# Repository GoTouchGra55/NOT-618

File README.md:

# NOT-618

_A custom CoreXY printer built on hopes and dreams._

**New Object Transmitter-618 / NOT-618** is a medium sized print volume _(220 × 220 × 220 mm)_ custom CoreXY 3d printer developed as a long term engineering project.

The project focuses on reliability, serviceability, and my open-source loyalty while serving as a platform for learning embedded systems, mechanical & PCB design, and firmware engineering.

## Features

- Automatic bed-leveling using BLTouch
- Independent dual Z motors
- Custom STM32F407-based controller (Vulcan-MK1)
- Marlin firmware support
- Fully open source design
- 24V power input

## Mechanical Design

### CAD: [OnShape URL](https://cad.onshape.com/documents/e82edfc86bb0a1665cdc75ee/w/ca3abfddd82f0954c06884bb/e/6fbd4bded61cf9b65a4d5030)

## PCB Design _(Vulcan-MK1)_

For GERBER file see [Vulcan-MK1](PCB/production/Vulcan-MK1.zip)

## Schematics

## Specifications

| Component       | Specification                       |
| --------------- | ----------------------------------- |
| Motion System   | CoreXY                              |
| Build Volume    | 220 × 220 × 220 mm                  |
| MCU             | STM32F407VET6                       |
| Stepper Drivers | TMC2209                             |
| Hotend          | E3D V6                              |
| Heated Bed      | Anycubic Kobra Go 24V               |
| Bed Probe       | BLTouch                             |
| Power Supply    | 24V 15A                             |
| Cooling         | 5015 Part Cooling + 3010 Hotend Fan |

## Assembly guide

1. Refer to the Onshape assembly for component placement and assembly order.
2. Do not carelessly wire the pcb and ensure good solder joints.

## ⚠️ Warning

1. Double-check polarity of capacitors and power input before powering the board. Otherwise you've made a fancy bomb :D
2. Use a 24v 15A SMPS for optimal performance. NEVER go higher than this.

## Flashing the Firmware

### 1. Build the Firmware

Compile Marlin using PlatformIO:

```bash
pio run -e STM32F407VE_black
```

After a successful build, the firmware will be located at:

```
.pio/build/STM32F407VE_black/firmware.bin
```

---

### 2. Copy the Firmware

1. Insert a microSD card (FAT32 formatted).
2. Copy `firmware.bin` to the root directory of the SD card.

The directory should look like:

```
/
├── firmware.bin
```

### 3. Flash the Board

1. Turn **off** the printer.
2. Insert the microSD card into the onboard SD card slot.
3. Power the board.

The STM32 bootloader will automatically detect `firmware.bin` and begin flashing.

Do **not** remove power during this process.

---

### 4. Verify the Flash

After flashing is complete:

- The board should boot into Marlin.
- Connect to the USB serial port.
- Send:

```gcode
M115
```

A successful response should report the installed Marlin version.

## Bill of Materials

| Name                   | Purpose                         | Quantity | Total Cost (USD) | Distributor              |
| ---------------------- | ------------------------------- | -------: | ---------------: | ------------------------ |
| Zip Ties               | Cable management                |        1 |            $1.04 | Daraz Nepal              |
| 22 AWG Wire            | For long connections            |        1 |            $4.08 | Daraz Nepal              |
| 18 AWG Wire            | For power connections           |        1 |            $5.34 | Daraz Nepal              |
| 24V 15A SMPS           | For power delivery              |        1 |           $31.14 | Daraz Nepal              |
| 0603 resistors         | For PCB                         |        1 |            $4.58 | Daraz Nepal              |
| 0805 capacitors        | For PCB                         |        1 |            $5.78 | Daraz Nepal              |
| Pitch Connectors       | For PCB                         |        1 |            $6.12 | Daraz Nepal              |
| JST XH Connectors      | For PCB                         |        1 |            $5.11 | Daraz Nepal              |
| 5015 24V Fan           | For cooling duct                |        1 |            $5.27 | Daraz Nepal              |
| Screws                 | For securing connections        |        1 |           $11.78 | Daraz Nepal              |
| 24V Heated Bed         | For printer                     |        1 |           $19.78 | Daraz Nepal              |
| PEI Sheet              | For printer                     |        1 |           $13.52 | Daraz Nepal              |
| GT2 idler              | For movement                    |        8 |           $25.24 | Daraz Nepal              |
| GT2 belt               | For movement                    |        1 |           $10.99 | Daraz Nepal              |
| E3D Hotend             | For printing                    |        1 |           $11.05 | Daraz Nepal              |
| Timing belt fixer      | For attaching belts             |        1 |             $3.1 | Daraz Nepal              |
| T-Nuts                 | For attaching extrusions        |        1 |            $5.84 | Daraz Nepal              |
| MK8 Extruder           | For filament output             |        1 |           $12.14 | Daraz Nepal              |
| Pancake Stepper        | For MK8 extruder                |        1 |           $12.04 | Daraz Nepal              |
| 3015 Fan               | For hotend cooling              |        1 |            $3.14 | Daraz Nepal              |
| Brass Inserts          | For fasteners                   |        1 |            $8.89 | Daraz Nepal              |
| Allen Keys             | For securing hex nuts           |        1 |            $1.75 | Daraz Nepal              |
| Limit switches         | For min-max feedback            |        2 |            $3.92 | Daraz Nepal              |
| Motor Coupler          | For attaching steppers and rods |        2 |            $2.44 | Daraz Nepal              |
| Threaded Rods          | For Z-axis movement             |        2 |            $7.54 | Daraz Nepal              |
| GT2 pulley             | For steppers                    |        2 |            $1.57 | Daraz Nepal              |
| Stepper Motors         | For movement                    |        4 |           $51.95 | Daraz Nepal              |
| LM10UU Bearings        | For linear movement             |        8 |           $18.49 | Daraz Nepal              |
| LM12UU Bearings        | For linear movement             |        4 |           $11.99 | Daraz Nepal              |
| Linear Shaft (300mm)   | For linear movement (12mm)      |        4 |           $67.98 | Daraz Nepal              |
| Linear Shaft (500mm)   | For linear movement (10mm)      |        2 |           $27.06 | Daraz Nepal              |
| Linear Shaft (330mm)   | For linear movement (10mm)      |        2 |           $19.10 | Daraz Nepal              |
| BLTouch                | For auto-bed leveling           |        1 |           $12.74 | Daraz Nepal              |
| 2040 Extrusion         | For printer stability           |        1 |              $15 | Daraz Nepal              |
| 2020 Extrusion (800mm) | Printer frame                   |        5 |          $117.08 | Daraz Nepal              |
| 2020 Extrusion (600mm) | Printer frame                   |        5 |          $104.98 | Daraz Nepal              |
| TMC2209 drivers        | To drive motors                 |        5 |           $37.26 | Daraz Nepal              |
| 12864 LCD              | To display stuff                |        1 |           $35.39 | Daraz Nepal              |
| 3-Way Connector        | To connect corners of extrusion |        8 |           $17.53 | Daraz Nepal              |
| Vulcan-MK1 PCB         | To control printer              |        1 |          $151.24 | JLCPCB                   |
| **Shipping**           |                                 |          |       **$29.72** | **Daraz Nepal & JLCPCB** |
| **Total**              |                                 |          |      **$944.16** |                          |

## License

### MIT-License - See [LICENSE](/LICENSE)

## Author 🧑‍💻

### [Shaurya Tamang](https://shauryatamang.netlify.app/)

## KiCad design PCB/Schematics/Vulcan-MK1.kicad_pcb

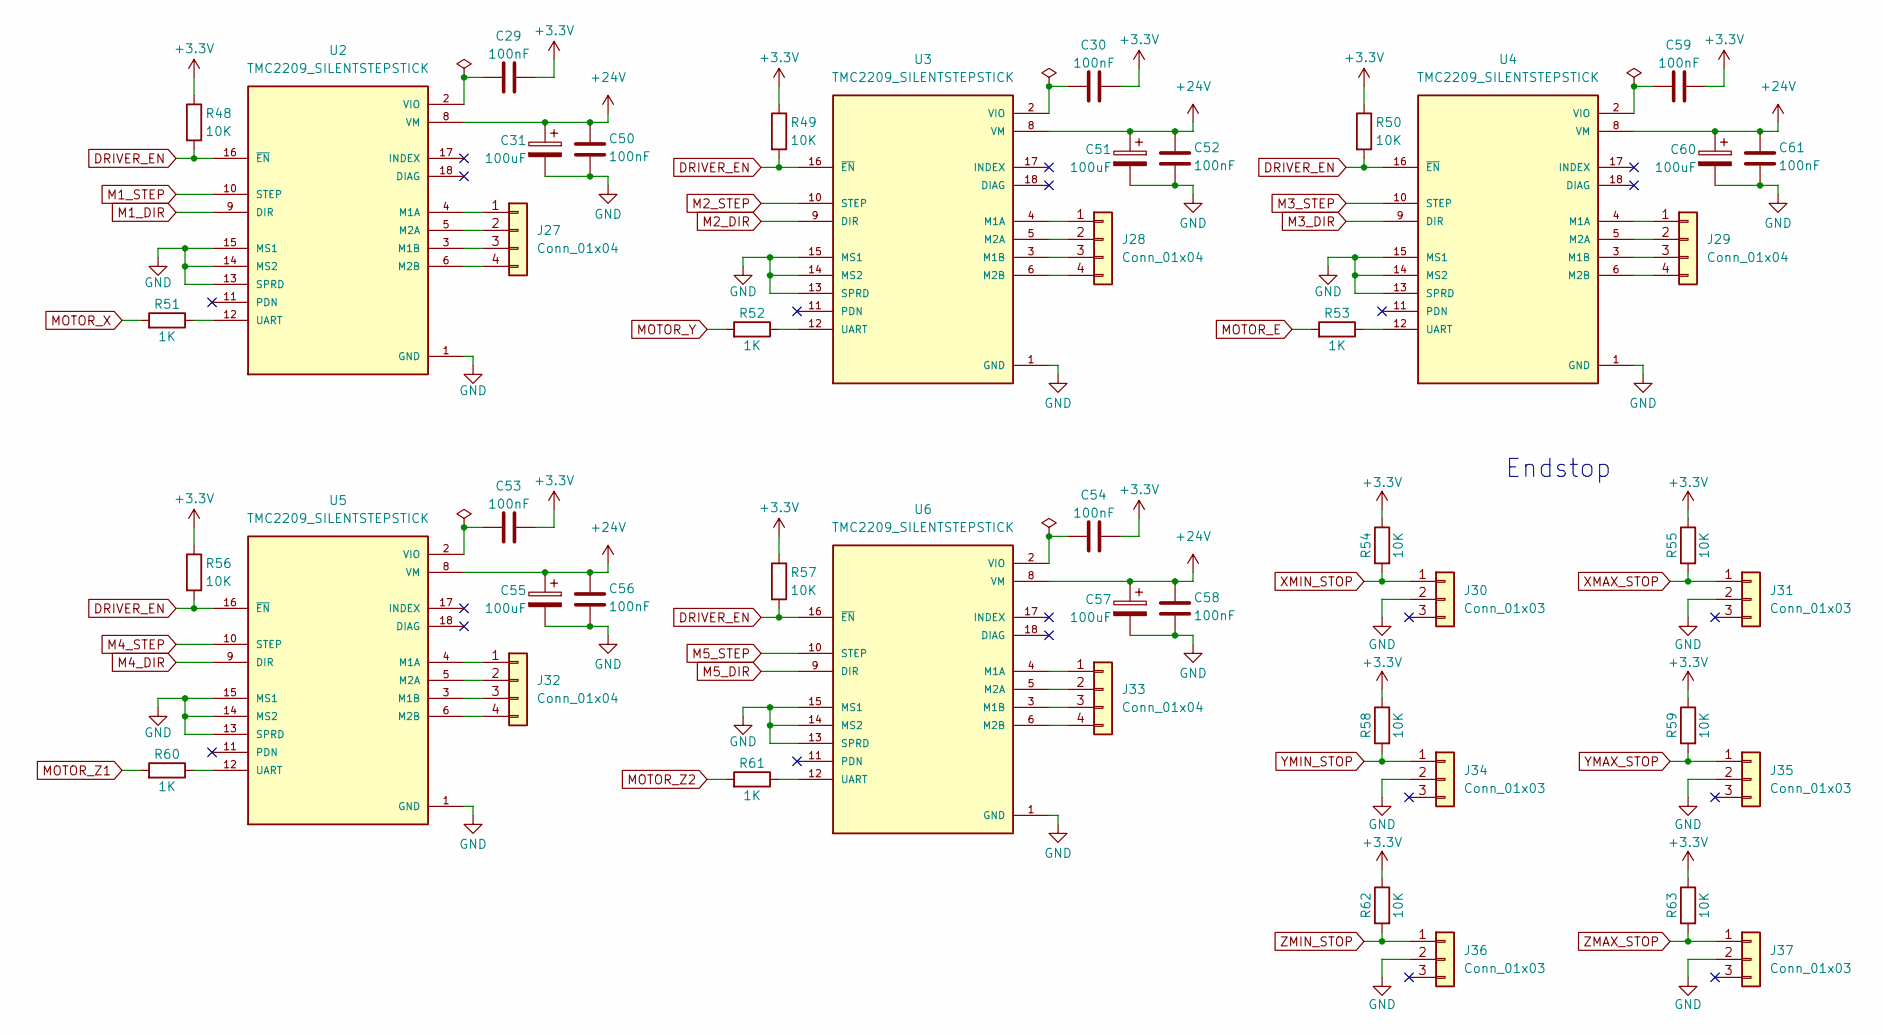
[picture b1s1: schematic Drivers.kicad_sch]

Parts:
C29, C30, C50, C52, C53, C54, C56, C58, C59, C61: 100nF; C_0603_1608Metric
C31, C51, C55, C57, C60: 100uF; CP_Elec_6.3x7.7
J27, J28, J29, J32, J33: Conn_01x04; JST_XH_B4B-XH-AM_1x04_P2.50mm_Vertical
J30, J31, J34, J35, J36, J37: Conn_01x03; JST_XH_B3B-XH-AM_1x03_P2.50mm_Vertical
R48, R49, R50, R54, R55, R56, R57, R58, R59, R62, R63: 10K; R_0603_1608Metric
R51, R52, R53, R60, R61: 1K; R_0603_1608Metric
U2, U3, U4, U5, U6: TMC2209_SILENTSTEPSTICK; MODULE_TMC2209_SILENTSTEPSTICK; PARTREV 1.20

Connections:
+3.3V: C29.1, C30.1, C53.1, C54.1, C59.1, R48.1, R49.1, R50.1, R54.1, R55.1, R56.1, R57.1, R58.1, R59.1, R62.1, R63.1; also elsewhere on the board
+24V: C31.1, C50.1, C51.1, C52.1, C55.1, C56.1, C57.1, C58.1, C60.1, C61.1, U2.8 (VM), U3.8 (VM), U4.8 (VM), U5.8 (VM), U6.8 (VM); also elsewhere on the board
DRIVER_EN: R48.2, R49.2, R50.2, R56.2, R57.2, U2.16 (~EN), U3.16 (~EN), U4.16 (~EN), U5.16 (~EN), U6.16 (~EN); also elsewhere on the board
GND: C31.2, C50.2, C51.2, C52.2, C55.2, C56.2, C57.2, C58.2, C60.2, C61.2, J30.2, J31.2, J34.2, J35.2, J36.2, J37.2, U2.1 (GND), U2.7 (GND), U2.13 (SPRD), U2.14 (MS2), U2.15 (MS1), U3.1 (GND), U3.7 (GND), U3.13 (SPRD), U3.14 (MS2), U3.15 (MS1), U4.1 (GND), U4.7 (GND), U4.13 (SPRD), U4.14 (MS2), U4.15 (MS1), U5.1 (GND), U5.7 (GND), U5.13 (SPRD), U5.14 (MS2), U5.15 (MS1), U6.1 (GND), U6.7 (GND), U6.13 (SPRD), U6.14 (MS2), U6.15 (MS1); also elsewhere on the board
M1_DIR: U2.9 (DIR); also elsewhere on the board
M1_STEP: U2.10 (STEP); also elsewhere on the board
M2_DIR: U3.9 (DIR); also elsewhere on the board
M2_STEP: U3.10 (STEP); also elsewhere on the board
M3_DIR: U4.9 (DIR); also elsewhere on the board
M3_STEP: U4.10 (STEP); also elsewhere on the board
M4_DIR: U5.9 (DIR); also elsewhere on the board
M4_STEP: U5.10 (STEP); also elsewhere on the board
M5_DIR: U6.9 (DIR); also elsewhere on the board
M5_STEP: U6.10 (STEP); also elsewhere on the board
MOTOR_E: R53.2; also elsewhere on the board
MOTOR_X: R51.2; also elsewhere on the board
MOTOR_Y: R52.2; also elsewhere on the board
MOTOR_Z1: R60.2; also elsewhere on the board
MOTOR_Z2: R61.2; also elsewhere on the board
unnamed: J27.1, U2.4 (M1A)
unnamed: J27.2, U2.5 (M2A)
unnamed: J27.3, U2.3 (M1B)
unnamed: J27.4, U2.6 (M2B)
unnamed: J28.1, U3.4 (M1A)
unnamed: J28.2, U3.5 (M2A)
unnamed: J28.3, U3.3 (M1B)
unnamed: J28.4, U3.6 (M2B)
unnamed: J29.1, U4.4 (M1A)
unnamed: J29.2, U4.5 (M2A)
unnamed: J29.3, U4.3 (M1B)
unnamed: J29.4, U4.6 (M2B)
unnamed: J32.1, U5.4 (M1A)
unnamed: J32.2, U5.5 (M2A)
unnamed: J32.3, U5.3 (M1B)
unnamed: J32.4, U5.6 (M2B)
unnamed: J33.1, U6.4 (M1A)
unnamed: J33.2, U6.5 (M2A)
unnamed: J33.3, U6.3 (M1B)
unnamed: J33.4, U6.6 (M2B)
unnamed: R51.1, U2.12 (UART)
unnamed: C29.2, U2.2 (VIO)
unnamed: R52.1, U3.12 (UART)
unnamed: C30.2, U3.2 (VIO)
unnamed: R53.1, U4.12 (UART)
unnamed: C59.2, U4.2 (VIO)
unnamed: R60.1, U5.12 (UART)
unnamed: C53.2, U5.2 (VIO)
unnamed: R61.1, U6.12 (UART)
unnamed: C54.2, U6.2 (VIO)
XMAX_STOP: J31.1, R55.2; also elsewhere on the board
XMIN_STOP: J30.1, R54.2; also elsewhere on the board
YMAX_STOP: J35.1, R59.2; also elsewhere on the board
YMIN_STOP: J34.1, R58.2; also elsewhere on the board
ZMAX_STOP: J37.1, R63.2; also elsewhere on the board
ZMIN_STOP: J36.1, R62.2; also elsewhere on the board

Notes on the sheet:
Endstop

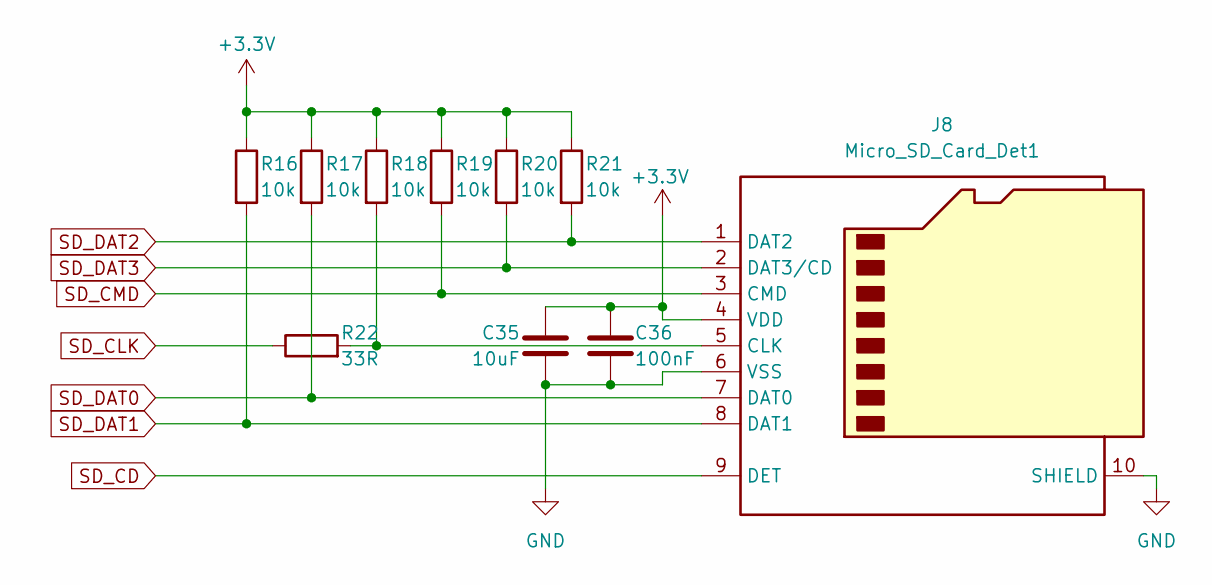
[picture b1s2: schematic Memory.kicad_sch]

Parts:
C35: 10uF; C_0805_2012Metric
C36: 100nF; C_0603_1608Metric
J8: Micro_SD_Card_Det1; microSD_HC_Wuerth_693072010801
R16, R17, R18, R19, R20, R21: 10k; R_0603_1608Metric
R22: 33R; R_0603_1608Metric

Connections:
+3.3V: C35.1, C36.1, J8.4 (VDD), R16.1, R17.1, R18.1, R19.1, R20.1, R21.1; also elsewhere on the board
GND: C35.2, C36.2, J8.6 (VSS), J8.10 (SHIELD); also elsewhere on the board
unnamed: J8.5 (CLK), R18.2, R22.2
SD_CD: J8.9 (DET); also elsewhere on the board
SD_CLK: R22.1; also elsewhere on the board
SD_CMD: J8.3 (CMD), R19.2; also elsewhere on the board
SD_DAT0: J8.7 (DAT0), R17.2; also elsewhere on the board
SD_DAT1: J8.8 (DAT1), R16.2; also elsewhere on the board
SD_DAT2: J8.1 (DAT2), R21.2; also elsewhere on the board
SD_DAT3: J8.2 (DAT3/CD), R20.2; also elsewhere on the board

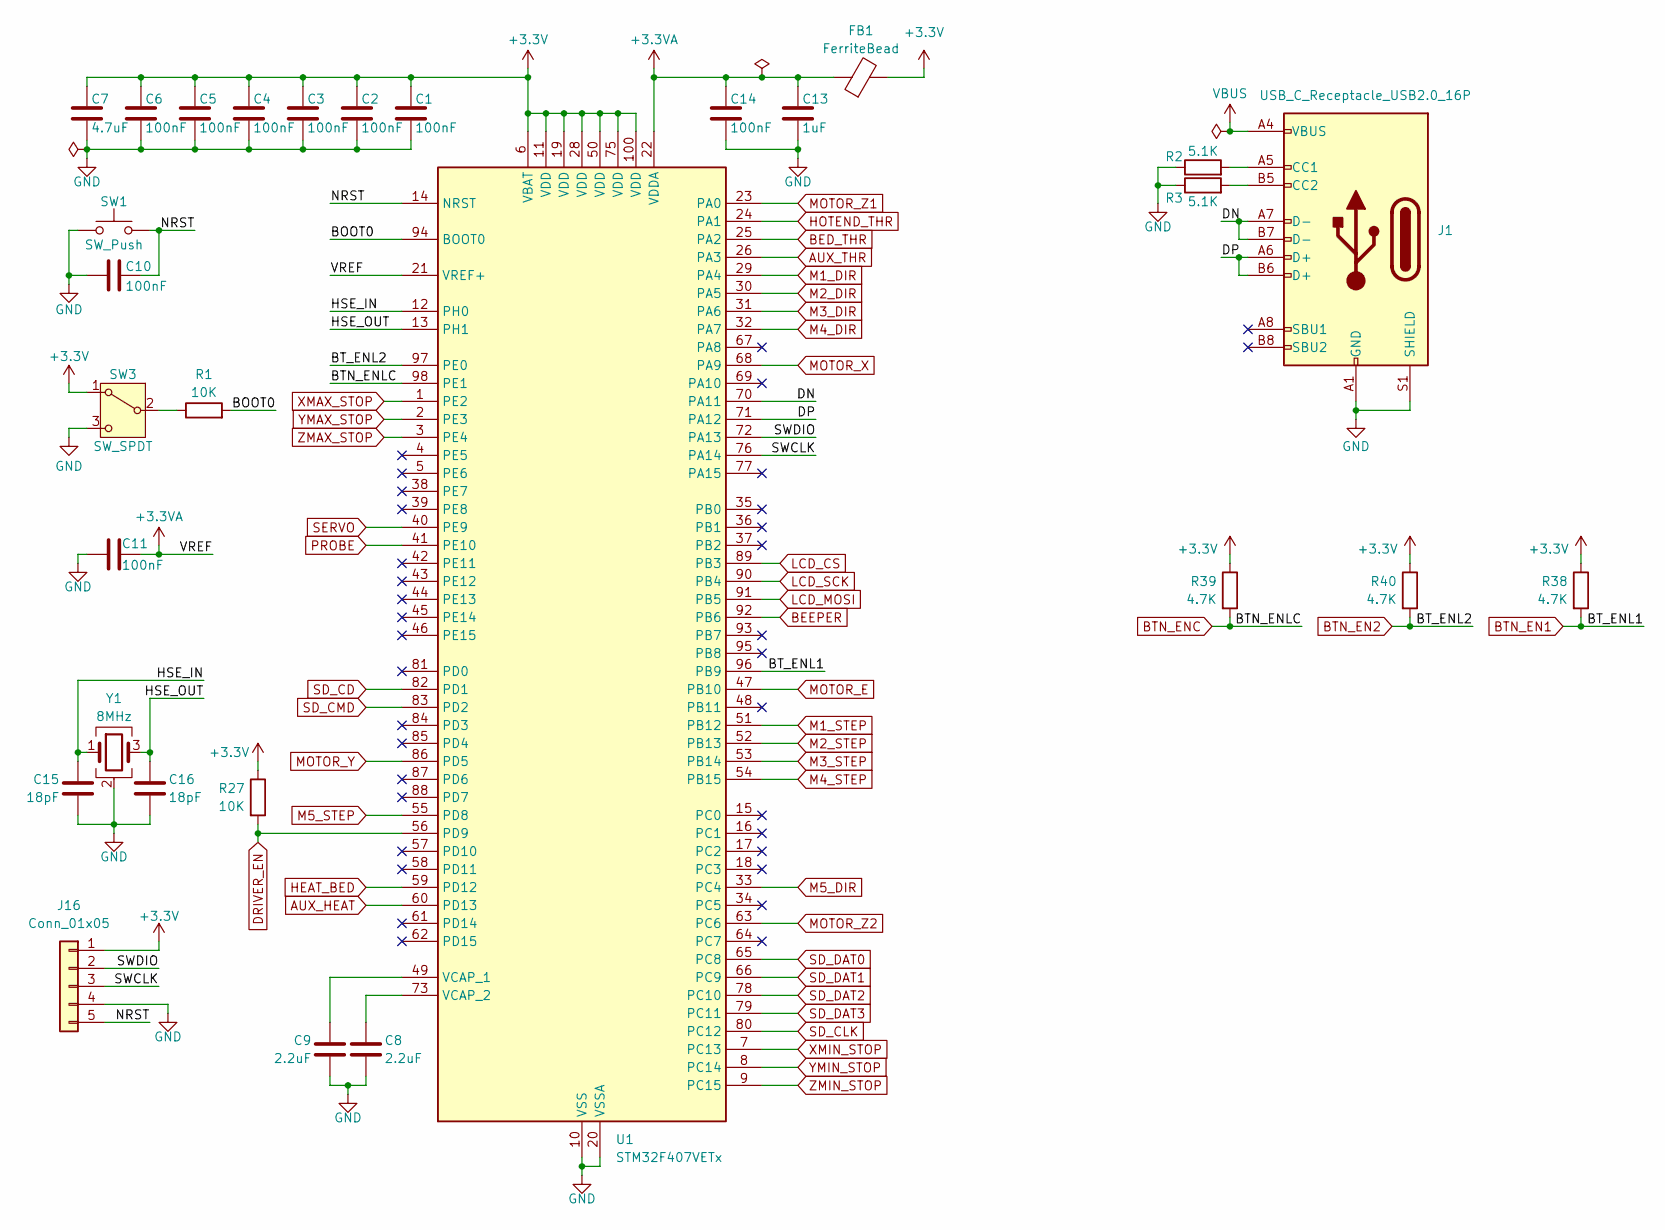
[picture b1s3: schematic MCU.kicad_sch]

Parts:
C1, C2, C3, C4, C5, C6, C10, C11, C14: 100nF; C_0603_1608Metric
C7: 4.7uF; C_0805_2012Metric
C8, C9: 2.2uF; C_0805_2012Metric
C13: 1uF; C_0805_2012Metric
C15, C16: 18pF; C_0603_1608Metric
FB1: FerriteBead; C_0603_1608Metric
J1: USB_C_Receptacle_USB2.0_16P; USB_C_Receptacle_GCT_USB4105-xx-A_16P_TopMnt_Horizontal
J16: Conn_01x05; JST_XH_B5B-XH-AM_1x05_P2.50mm_Vertical
R1, R27: 10K; R_0603_1608Metric
R2, R3: 5.1K; R_0603_1608Metric
R38, R39, R40: 4.7K; R_0603_1608Metric
SW1: SW_Push; SW_SPST_PTS647_Sx38
SW3: SW_SPDT; SW_SPDT_PCM12
U1: STM32F407VETx; LQFP-100_14x14mm_P0.5mm
Y1: 8MHz; Crystal_SMD_3225-4Pin_3.2x2.5mm

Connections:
+3.3V: C1.1, C2.1, C3.1, C4.1, C5.1, C6.1, C7.1, FB1.2, J16.1, R27.1, R38.1, R39.1, R40.1, SW3.1 (A), U1.6 (VBAT), U1.11 (VDD), U1.19 (VDD), U1.28 (VDD), U1.50 (VDD), U1.75 (VDD), U1.100 (VDD); also elsewhere on the board
+3.3VA: C11.2, C13.1, C14.1, FB1.1, U1.21 (VREF+), U1.22 (VDDA)
/MCU/BOOT0: R1.2, U1.94 (BOOT0)
/MCU/DN: J1.A7 (D-), J1.B7 (D-), U1.70 (PA11)
/MCU/DP: J1.A6 (D+), J1.B6 (D+), U1.71 (PA12)
/MCU/HSE_IN: C15.2, U1.12 (PH0), Y1.1
/MCU/HSE_OUT: C16.2, U1.13 (PH1), Y1.3
/MCU/NRST: C10.2, J16.5, SW1.2, U1.14 (NRST)
/MCU/SWCLK: J16.3, U1.76 (PA14)
/MCU/SWDIO: J16.2, U1.72 (PA13)
AUX_HEAT: U1.60 (PD13); also elsewhere on the board
AUX_THR: U1.26 (PA3); also elsewhere on the board
BED_THR: U1.25 (PA2); also elsewhere on the board
BEEPER: U1.92 (PB6); also elsewhere on the board
BTN_EN1: R38.2, U1.96 (PB9); also elsewhere on the board
BTN_EN2: R40.2, U1.97 (PE0); also elsewhere on the board
BTN_ENC: R39.2, U1.98 (PE1); also elsewhere on the board
DRIVER_EN: R27.2, U1.56 (PD9); also elsewhere on the board
GND: C1.2, C2.2, C3.2, C4.2, C5.2, C6.2, C7.2, C8.1, C9.1, C10.1, C11.1, C13.2, C14.2, C15.1, C16.1, J1.A1 (GND), J1.A12 (GND), J1.B1 (GND), J1.B12 (GND), J1.S1 (SHIELD), J16.4, R2.1, R3.1, SW1.1, SW3.3 (C), U1.10 (VSS), U1.20 (VSSA), U1.27 (VSS), U1.74 (VSS), U1.99 (VSS), Y1.2 (G), Y1.4 (G); also elsewhere on the board
HEAT_BED: U1.59 (PD12); also elsewhere on the board
HOTEND_THR: U1.24 (PA1); also elsewhere on the board
LCD_CS: U1.89 (PB3); also elsewhere on the board
LCD_MOSI: U1.91 (PB5); also elsewhere on the board
LCD_SCK: U1.90 (PB4); also elsewhere on the board
M1_DIR: U1.29 (PA4); also elsewhere on the board
M1_STEP: U1.51 (PB12); also elsewhere on the board
M2_DIR: U1.30 (PA5); also elsewhere on the board
M2_STEP: U1.52 (PB13); also elsewhere on the board
M3_DIR: U1.31 (PA6); also elsewhere on the board
M3_STEP: U1.53 (PB14); also elsewhere on the board
M4_DIR: U1.32 (PA7); also elsewhere on the board
M4_STEP: U1.54 (PB15); also elsewhere on the board
M5_DIR: U1.33 (PC4); also elsewhere on the board
M5_STEP: U1.55 (PD8); also elsewhere on the board
MOTOR_E: U1.47 (PB10); also elsewhere on the board
MOTOR_X: U1.68 (PA9); also elsewhere on the board
MOTOR_Y: U1.86 (PD5); also elsewhere on the board
MOTOR_Z1: U1.23 (PA0); also elsewhere on the board
MOTOR_Z2: U1.63 (PC6); also elsewhere on the board
unnamed: J1.A5 (CC1), R2.2
unnamed: J1.B5 (CC2), R3.2
unnamed: R1.1, SW3.2 (B)
unnamed: C9.2, U1.49 (VCAP_1)
unnamed: C8.2, U1.73 (VCAP_2)
PROBE: U1.41 (PE10); also elsewhere on the board
SD_CD: U1.82 (PD1); also elsewhere on the board
SD_CLK: U1.80 (PC12); also elsewhere on the board
SD_CMD: U1.83 (PD2); also elsewhere on the board
SD_DAT0: U1.65 (PC8); also elsewhere on the board
SD_DAT1: U1.66 (PC9); also elsewhere on the board
SD_DAT2: U1.78 (PC10); also elsewhere on the board
SD_DAT3: U1.79 (PC11); also elsewhere on the board
SERVO: U1.40 (PE9); also elsewhere on the board
VBUS: J1.A4 (VBUS), J1.A9 (VBUS), J1.B4 (VBUS), J1.B9 (VBUS); also elsewhere on the board
XMAX_STOP: U1.1 (PE2); also elsewhere on the board
XMIN_STOP: U1.7 (PC13); also elsewhere on the board
YMAX_STOP: U1.2 (PE3); also elsewhere on the board
YMIN_STOP: U1.8 (PC14); also elsewhere on the board
ZMAX_STOP: U1.3 (PE4); also elsewhere on the board
ZMIN_STOP: U1.9 (PC15); also elsewhere on the board

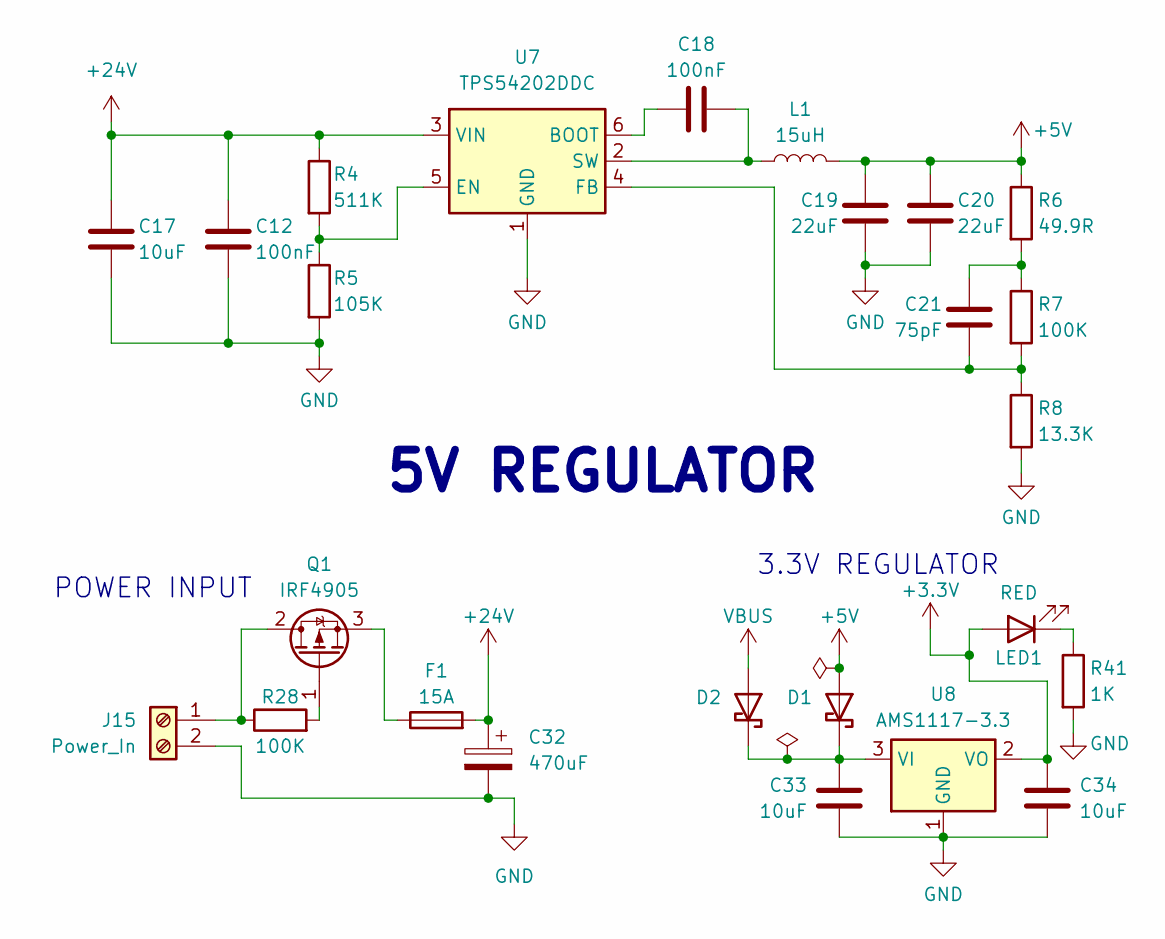
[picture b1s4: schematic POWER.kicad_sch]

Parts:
C12, C18: 100nF; C_0603_1608Metric
C17, C33, C34: 10uF; C_0805_2012Metric
C19, C20: 22uF; C_0805_2012Metric
C21: 75pF; C_0603_1608Metric
C32: 470uF; C_Elec_8x10.2
D1, D2: D_Schottky; D_0603_1608Metric
F1: 15A; Fuse_1206_3216Metric
J15: Power_In; TerminalBlock_Phoenix_MKDS-1,5-2-5.08_1x02_P5.08mm_Horizont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
L1: 15uH; L_Cenker_CKCS4030
LED1: RED; LED_0603_1608Metric
Q1: IRF4905; TRANS_IRF3205S
R4: 511K; R_0603_1608Metric
R5: 105K; R_0603_1608Metric
R6: 49.9R; R_0603_1608Metric
R7, R28: 100K; R_0603_1608Metric
R8: 13.3K; R_0603_1608Metric
R41: 1K; R_0603_1608Metric
U7: TPS54202DDC; SOT-23-6
U8: AMS1117-3.3; SOT-223-3_TabPin2

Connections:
+3.3V: C34.1, LED1.2 (A), U8.2 (VO); also elsewhere on the board
+5V: C19.1, C20.1, D1.2 (A), L1.2, R6.1; also elsewhere on the board
+24V: C12.1, C17.1, C32.1, F1.2, R4.1, U7.3 (VIN); also elsewhere on the board
GND: C12.2, C17.2, C19.2, C20.2, C32.2, C33.2, C34.2, J15.2, R5.2, R8.2, R41.2, U7.1 (GND), U8.1 (GND); also elsewhere on the board
unnamed: C21.1, R6.2, R7.1
unnamed: C33.1, D1.1 (K), D2.1 (K), U8.3 (VI)
unnamed: J15.1, Q1.2 (D), R28.1
unnamed: LED1.1 (K), R41.1
unnamed: Q1.1 (G), R28.2
unnamed: F1.1, Q1.3 (S)
unnamed: C18.1, U7.6 (BOOT)
unnamed: R4.2, R5.1, U7.5 (EN)
unnamed: C21.2, R7.2, R8.1, U7.4 (FB)
unnamed: C18.2, L1.1, U7.2 (SW)
VBUS: D2.2 (A); also elsewhere on the board

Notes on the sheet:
3.3V REGULATOR
POWER INPUT
5V REGULATOR

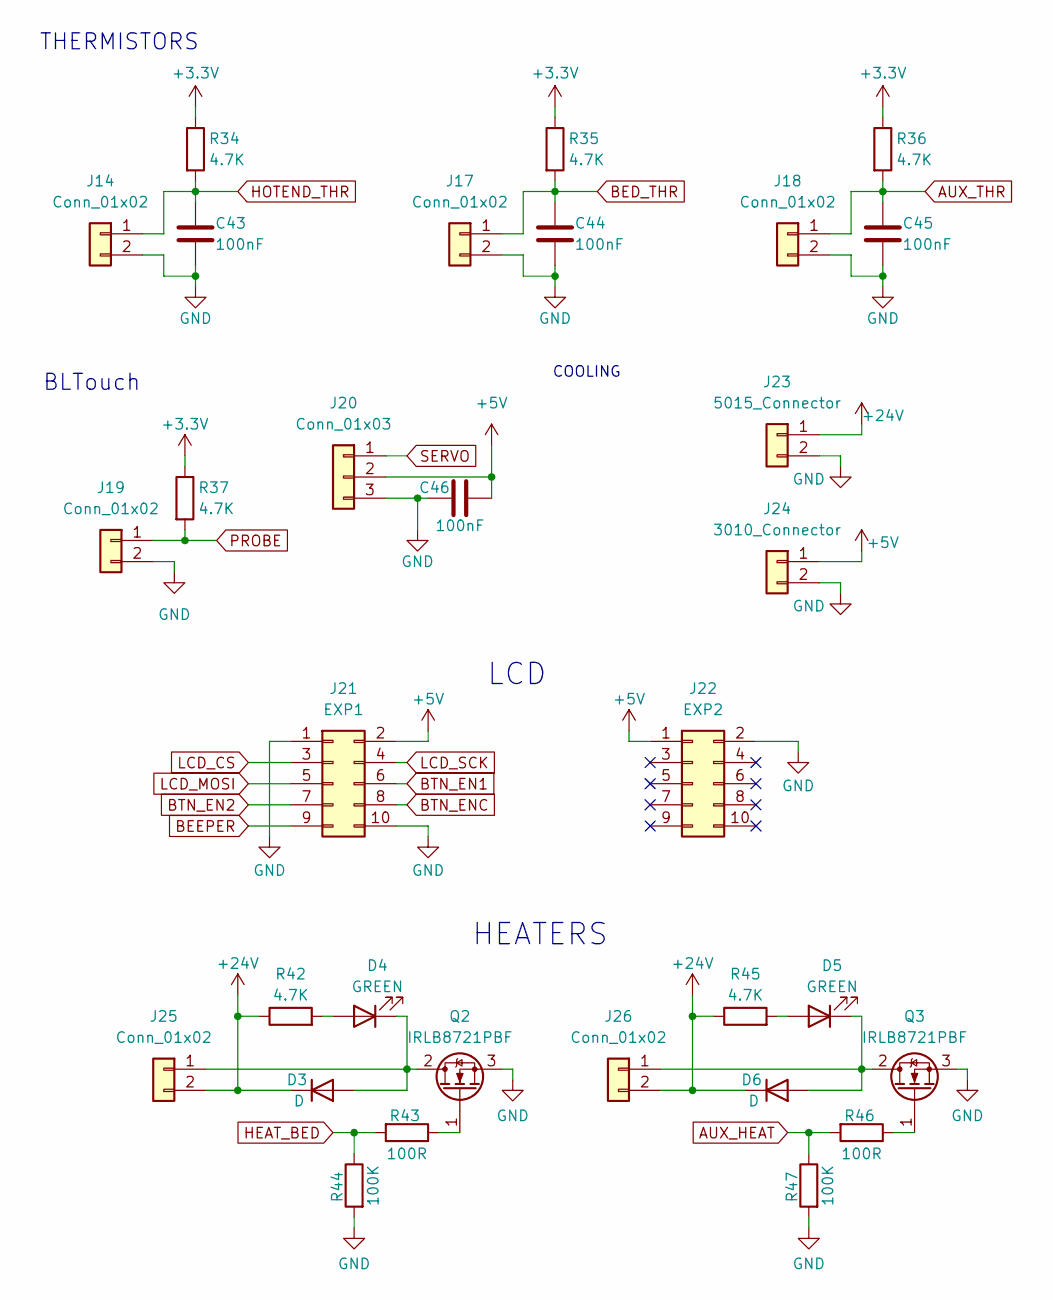
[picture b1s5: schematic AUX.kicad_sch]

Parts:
C43, C44, C45, C46: 100nF; C_0603_1608Metric
D3, D6: D; D_0603_1608Metric
D4, D5: GREEN; LED_0603_1608Metric
J14, J17, J18, J19, J25, J26: Conn_01x02; JST_XH_B2B-XH-AM_1x02_P2.50mm_Vertical
J20: Conn_01x03; JST_XH_B3B-XH-AM_1x03_P2.50mm_Vertical
J21: EXP1; IDC-Header_2x05_P2.54mm_Vertical
J22: EXP2; IDC-Header_2x05_P2.54mm_Vertical
J23: 5015_Connector; JST_XH_B2B-XH-AM_1x02_P2.50mm_Vertical
J24: 3010_Connector; JST_XH_B2B-XH-AM_1x02_P2.50mm_Vertical
Q2, Q3: IRLB8721PBF; TO252_AOS
R34, R35, R36, R37, R42, R45: 4.7K; R_0603_1608Metric
R43, R46: 100R; R_0603_1608Metric
R44, R47: 100K; R_0603_1608Metric

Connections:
+3.3V: R34.1, R35.1, R36.1, R37.1; also elsewhere on the board
+5V: C46.1, J20.2, J21.2, J22.1, J24.1; also elsewhere on the board
+24V: D3.1 (K), D6.1 (K), J23.1, J25.2, J26.2, R42.1, R45.1; also elsewhere on the board
AUX_HEAT: R46.2, R47.1; also elsewhere on the board
AUX_THR: C45.1, J18.1, R36.2; also elsewhere on the board
BED_THR: C44.1, J17.1, R35.2; also elsewhere on the board
BEEPER: J21.9; also elsewhere on the board
BTN_EN1: J21.6; also elsewhere on the board
BTN_EN2: J21.7; also elsewhere on the board
BTN_ENC: J21.8; also elsewhere on the board
GND: C43.2, C44.2, C45.2, C46.2, J14.2, J17.2, J18.2, J19.2, J20.3, J21.1, J21.10, J22.2, J23.2, J24.2, Q2.3 (S), Q3.3 (S), R44.2, R47.2; also elsewhere on the board
HEAT_BED: R43.2, R44.1; also elsewhere on the board
HOTEND_THR: C43.1, J14.1, R34.2; also elsewhere on the board
LCD_CS: J21.3; also elsewhere on the board
LCD_MOSI: J21.5; also elsewhere on the board
LCD_SCK: J21.4; also elsewhere on the board
unnamed: D3.2 (A), D4.1 (K), J25.1, Q2.2 (D)
unnamed: D4.2 (A), R42.2
unnamed: D5.2 (A), R45.2
unnamed: D5.1 (K), D6.2 (A), J26.1, Q3.2 (D)
unnamed: Q2.1 (G), R43.1
unnamed: Q3.1 (G), R46.1
PROBE: J19.1, R37.2; also elsewhere on the board
SERVO: J20.1; also elsewhere on the board

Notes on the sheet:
HEATERS
BLTouch
THERMISTORS
COOLING
LCD

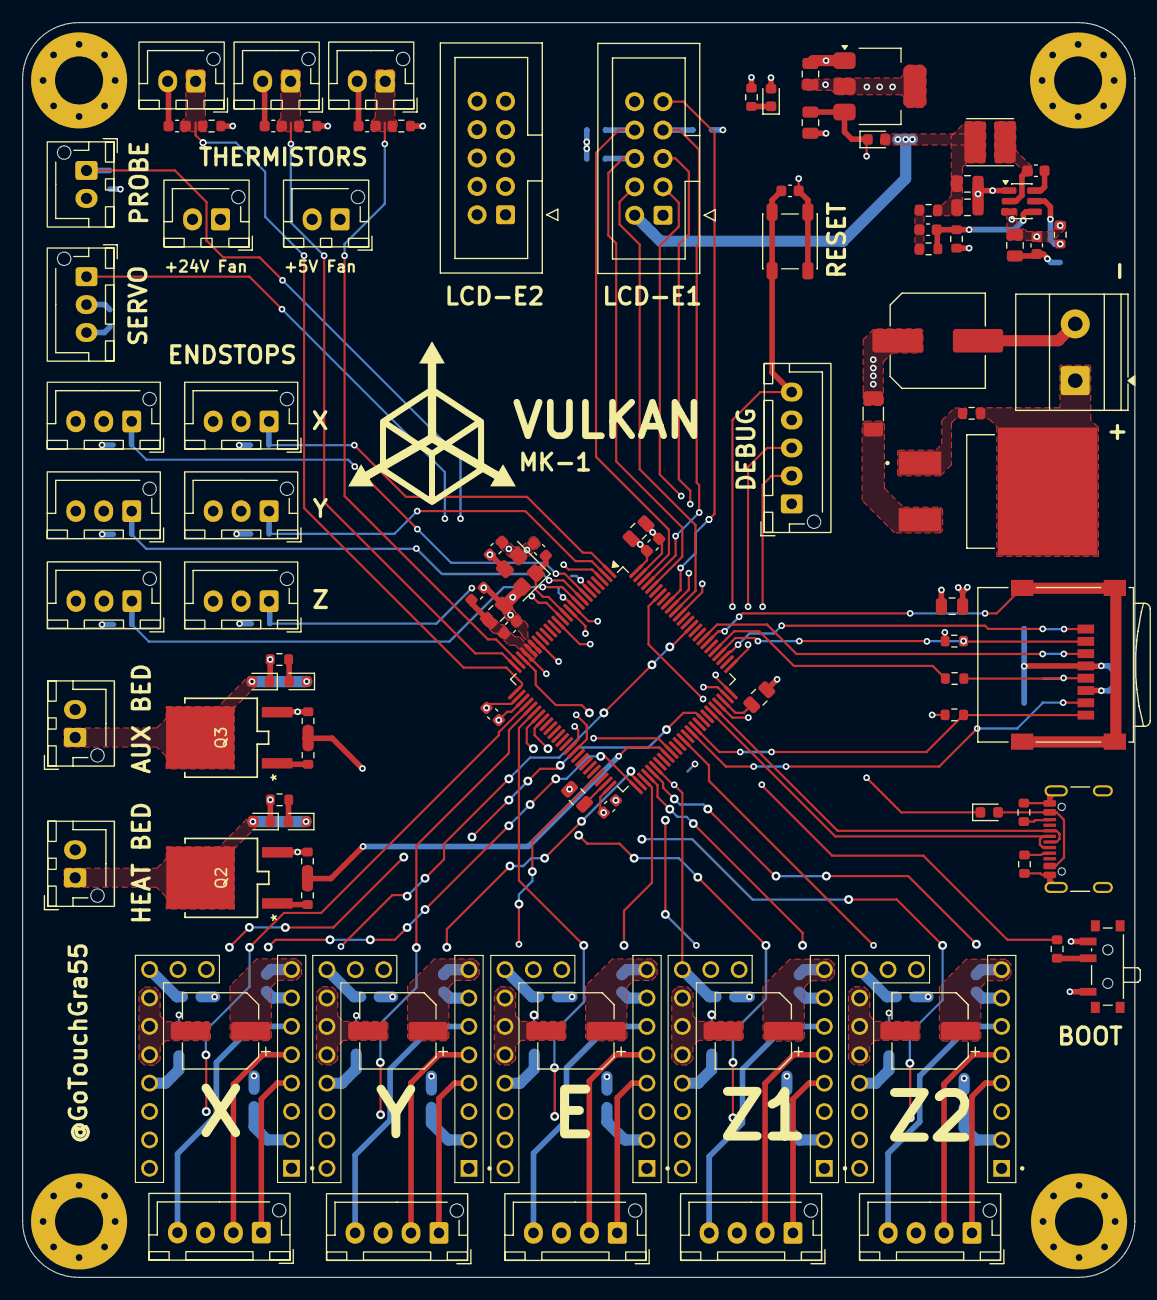
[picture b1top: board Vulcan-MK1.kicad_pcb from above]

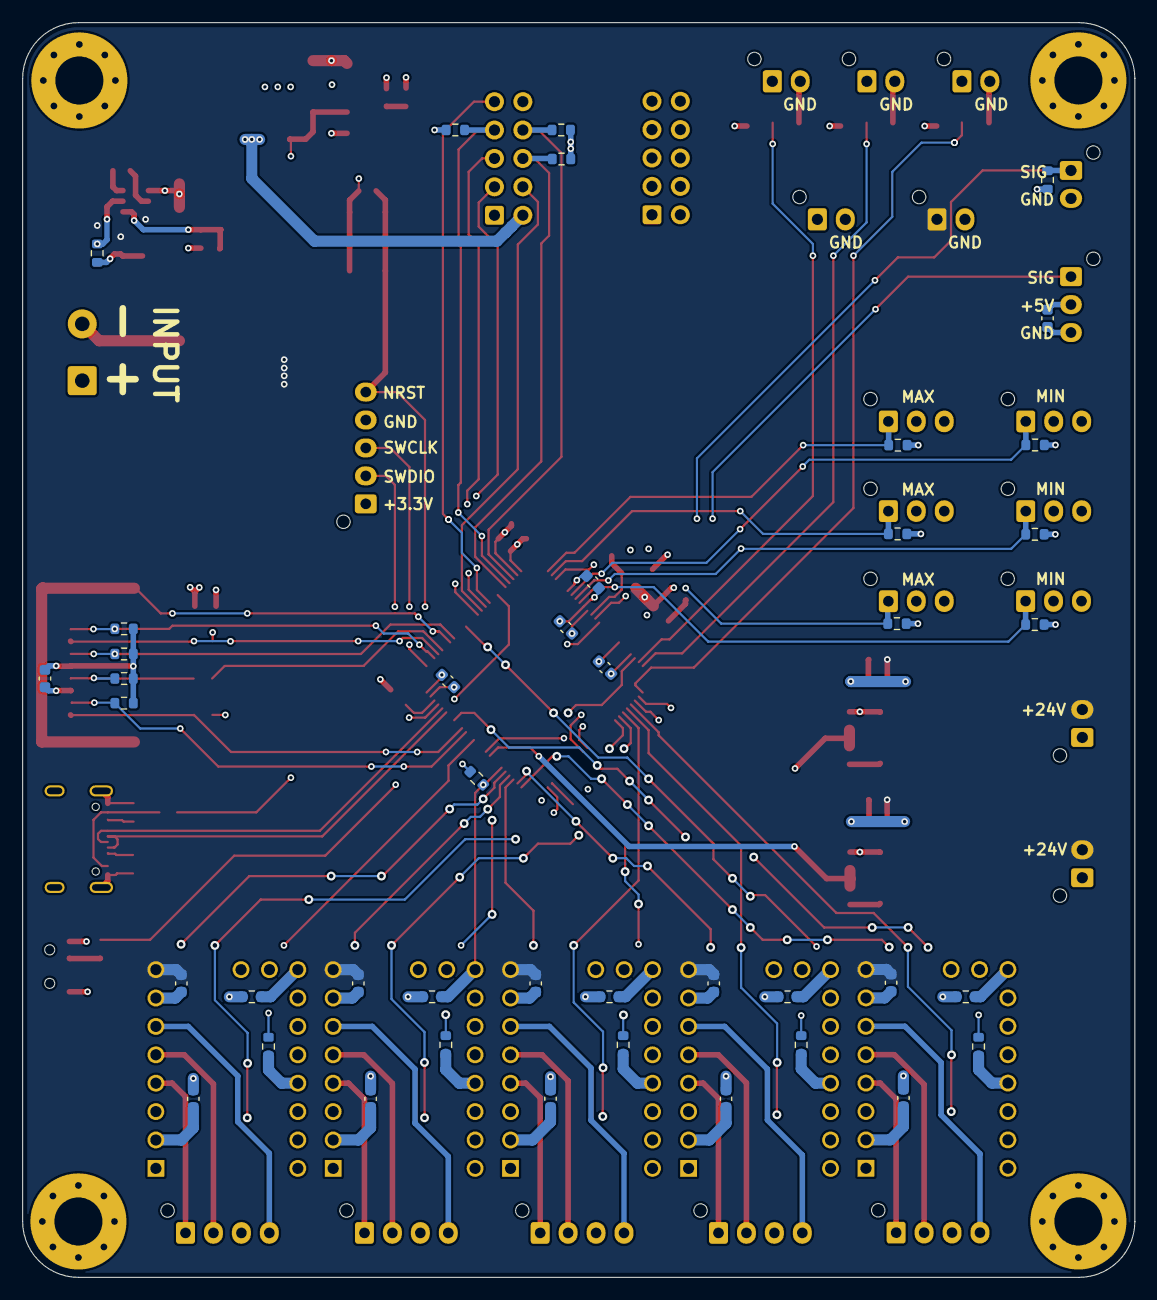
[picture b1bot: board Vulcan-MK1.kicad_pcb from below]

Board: 4 copper layers, 99.5 x 112.2 mm, 142 parts (42 on the bottom side), 109 nets.

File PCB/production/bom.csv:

Designator,Footprint,Quantity,Value,LCSC Part #
"C1, C10, C11, C12, C14, C18, C2, C29, C3, C30, C36, C4, C43, C44, C45, C46, C5, C50, C52, C53, C54, C56, C58, C59, C6, C61",0603,26,100nF,
C13,0805,1,1uF,
"C15, C16",0603,2,18pF,
"C17, C33, C34, C35",0805,4,10uF,
"C19, C20",0805,2,22uF,
C21,0603,1,75pF,
"C31, C51, C55, C57, C60",CP_Elec_6.3x7.7,5,100uF,
C32,C_Elec_8x10.2,1,470uF,
C7,0805,1,4.7uF,
"C8, C9",0805,2,2.2uF,
"D1, D2",0603,2,D_Schottky,
"D3, D6",0603,2,D,
"D4, D5",0603,2,GREEN,
F1,1206,1,15A,
FB1,0603,1,FerriteBead,
J1,USB_C_Receptacle_GCT_USB4105-xx-A_16P_TopMnt_Horizontal,1,USB_C_Receptacle_USB2.0_16P,
"J14, J17, J18, J19, J25, J26",JST_XH_B2B-XH-AM_1x02_P2.50mm_Vertical,6,Conn_01x02,
J15,"TerminalBlock_Phoenix_MKDS-1,5-2-5.08_1x02_P5.08mm_Horizontal",1,Power_In,
J16,JST_XH_B5B-XH-AM_1x05_P2.50mm_Vertical,1,Conn_01x05,
"J20, J30, J31, J34, J35, J36, J37",JST_XH_B3B-XH-AM_1x03_P2.50mm_Vertical,7,Conn_01x03,
J21,IDC-Header_2x05_P2.54mm_Vertical,1,EXP1,
J22,IDC-Header_2x05_P2.54mm_Vertical,1,EXP2,
J23,JST_XH_B2B-XH-AM_1x02_P2.50mm_Vertical,1,5015_Connector,
J24,JST_XH_B2B-XH-AM_1x02_P2.50mm_Vertical,1,3010_Connector,
"J27, J28, J29, J32, J33",JST_XH_B4B-XH-AM_1x04_P2.50mm_Vertical,5,Conn_01x04,
J8,microSD_HC_Wuerth_693072010801,1,Micro_SD_Card_Det1,
L1,L_Cenker_CKCS4030,1,15uH,
LED1,0603,1,RED,
Q1,TRANS_IRF3205S,1,IRF4905,
"Q2, Q3",TO252_AOS,2,IRLB8721PBF,
"R1, R16, R17, R18, R19, R20, R21, R27, R48, R49, R50, R54, R55, R56, R57, R58, R59, R62, R63",0603,19,10K,
"R2, R3",0603,2,5.1K,
R22,0603,1,33R,
"R28, R44, R47, R7",0603,4,100K,
"R34, R35, R36, R37, R38, R39, R40, R42, R45",0603,9,4.7K,
R4,0603,1,511K,
"R41, R51, R52, R53, R60, R61",0603,6,1K,
"R43, R46",0603,2,100R,
R5,0603,1,105K,
R6,0603,1,49.9R,
R8,0603,1,13.3K,
SW1,SW_SPST_PTS647_Sx38,1,SW_Push,
SW3,SW_SPDT_PCM12,1,SW_SPDT,
U1,LQFP-100_14x14mm_P0.5mm,1,STM32F407VETx,
"U2, U3, U4, U5, U6",MODULE_TMC2209_SILENTSTEPSTICK,5,TMC2209_SILENTSTEPSTICK,
U7,SOT-23-6,1,TPS54202DDC,
U8,SOT-223-3_TabPin2,1,AMS1117-3.3,
Y1,Crystal_SMD_3225-4Pin_3.2x2.5mm,1,8MHz,

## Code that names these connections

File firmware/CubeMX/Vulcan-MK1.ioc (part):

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Mcu.Name=STM32F407V(E-G)Tx
Mcu.Package=LQFP100
Mcu.UserName=STM32F407VETx
PA0-WKUP.GPIOParameters=GPIO_Label
PA0-WKUP.GPIO_Label=MOTOR_Z1
PA0-WKUP.Mode=Half_duplex(single_wire_mode)
PA0-WKUP.Signal=UART4_TX
PA1.GPIOParameters=GPIO_Label
PA1.GPIO_Label=HOTEND_THR
PA1.Signal=ADCx_IN1
PA10.Mode=OTG/Dual_Role_Device
PA10.Signal=USB_OTG_FS_ID
PA11.Mode=OTG/Dual_Role_Device
PA11.Signal=USB_OTG_FS_DM
PA12.Mode=OTG/Dual_Role_Device
PA12.Signal=USB_OTG_FS_DP
PA13.Mode=Serial_Wire
PA13.Signal=SYS_JTMS-SWDIO
PA14.Mode=Serial_Wire
PA14.Signal=SYS_JTCK-SWCLK
PA2.GPIOParameters=GPIO_Label
PA2.GPIO_Label=BED_THR
PA2.Signal=ADCx_IN2
PA3.GPIOParameters=GPIO_Label
PA3.GPIO_Label=AUX_THR
PA3.Signal=ADCx_IN3
PA4.GPIOParameters=GPIO_Label
PA4.GPIO_Label=MX_DIR
PA4.Signal=GPIO_Output
PA5.GPIOParameters=GPIO_Label
PA5.GPIO_Label=MY_DIR
PA5.Signal=GPIO_Output
PA6.GPIOParameters=GPIO_Label
PA6.GPIO_Label=ME_DIR
PA6.Signal=GPIO_Output
PA7.GPIOParameters=GPIO_Label
PA7.GPIO_Label=MZ1_DIR
PA7.Signal=GPIO_Output
PA9.GPIOParameters=GPIO_Label
PA9.GPIO_Label=MOTOR_X
PA9.Mode=Half_duplex(single_wire_mode)
PA9.Signal=USART1_TX
PB10.GPIOParameters=GPIO_Label
PB10.GPIO_Label=MOTOR_E
PB10.Mode=Half_duplex(single_wire_mode)
PB10.Signal=USART3_TX
PB12.GPIOParameters=GPIO_Label
PB12.GPIO_Label=MX_STEP
PB12.Signal=GPIO_Output
PB13.GPIOParameters=GPIO_Label
PB13.GPIO_Label=MY_STEP
PB13.Signal=GPIO_Output
PB14.GPIOParameters=GPIO_Label
PB14.GPIO_Label=ME_STEP
PB14.Signal=GPIO_Output
PB15.GPIOParameters=GPIO_Label
PB15.GPIO_Label=MZ1_STEP
PB15.Signal=GPIO_Output
PB3.GPIOParameters=GPIO_Label
PB3.GPIO_Label=LCD_CS
PB3.Signal=GPIO_Output
PB4.GPIOParameters=GPIO_Label
PB4.GPIO_Label=LCD_SCK
PB4.Signal=GPIO_Output
PB5.GPIOParameters=GPIO_Label
PB5.GPIO_Label=LCD_MOSI
PB5.Signal=GPIO_Output
PB6.GPIOParameters=GPIO_Label
PB6.GPIO_Label=BEEPER
PB6.Signal=GPIO_Output
PB9.GPIOParameters=GPIO_Label
PB9.GPIO_Label=BTN_EN1
PB9.Signal=GPIO_Input
PC10.Mode=SD_4_bits_Wide_bus
PC10.Signal=SDIO_D2
PC11.Mode=SD_4_bits_Wide_bus
PC11.Signal=SDIO_D3
PC12.Mode=SD_4_bits_Wide_bus
PC12.Signal=SDIO_CK
PC13-ANTI_TAMP.GPIOParameters=GPIO_Label
PC13-ANTI_TAMP.GPIO_Label=XMIN_STOP
PC13-ANTI_TAMP.Signal=GPXTI13
PC14-OSC32_IN.GPIOParameters=GPIO_Label
PC14-OSC32_IN.GPIO_Label=YMIN_STOP
PC14-OSC32_IN.Signal=GPXTI14
PC15-OSC32_OUT.GPIOParameters=GPIO_Label
PC15-OSC32_OUT.GPIO_Label=ZMIN_STOP
PC15-OSC32_OUT.Signal=GPXTI15
PC4.Signal=GPIO_Output
PC6.GPIOParameters=GPIO_Label
PC6.GPIO_Label=MOTOR_Z2
PC6.Mode=Half_duplex(single_wire_mode)
PC6.Signal=USART6_TX
PC8.Mode=SD_4_bits_Wide_bus
PC8.Signal=SDIO_D0
PC9.Mode=SD_4_bits_Wide_bus
PC9.Signal=SDIO_D1
PD1.GPIOParameters=GPIO_Label
PD1.GPIO_Label=SD_CD
PD1.Signal=GPIO_Input
PD12.GPIOParameters=GPIO_Label
PD12.GPIO_Label=HEAT_BED
PD12.Signal=S_TIM4_CH1
PD13.GPIOParameters=GPIO_Label
PD13.GPIO_Label=AUX_HEAT
PD13.Signal=S_TIM4_CH2
PD2.Mode=SD_4_bits_Wide_bus
PD2.Signal=SDIO_CMD
PD5.GPIOParameters=GPIO_Label
PD5.GPIO_Label=MOTOR_Y
PD5.Mode=Half_duplex(single_wire_mode)
PD5.Signal=USART2_TX
PD8.GPIOParameters=GPIO_Label
PD8.GPIO_Label=MZ2_STEP
PD8.Signal=GPIO_Output
PD9.GPIOParameters=GPIO_Label
PD9.GPIO_Label=DR_EN
PD9.Signal=GPIO_Output
PE0.GPIOParameters=GPIO_Label
PE0.GPIO_Label=BTN_EN2
PE0.Signal=GPIO_Input
PE1.GPIOParameters=GPIO_Label
PE1.GPIO_Label=BEN_ENC
PE1.Signal=GPIO_Input
PE10.GPIOParameters=GPIO_Label
PE10.GPIO_Label=PROBE
PE10.Signal=GPXTI10
PE2.GPIOParameters=GPIO_Label
PE2.GPIO_Label=XMAX_STOP
PE2.Signal=GPXTI2
PE3.GPIOParameters=GPIO_Label
PE3.GPIO_Label=YMAX_STOP
PE3.Signal=GPXTI3
PE4.GPIOParameters=GPIO_Label
PE4.GPIO_Label=ZMAX_STOP
PE4.Signal=GPXTI4
PE9.GPIOParameters=GPIO_Label
PE9.GPIO_Label=SERVO
PE9.Signal=S_TIM1_CH1
PH0-OSC_IN.Mode=HSE-External-Oscillator
PH0-OSC_IN.Signal=RCC_OSC_IN
PH1-OSC_OUT.Mode=HSE-External-Oscillator
PH1-OSC_OUT.Signal=RCC_OSC_OUT
RCC.HSE_VALUE=8000000
RCC.SYSCLKFreq_VALUE=72000000
RCC.SYSCLKSource=RCC_SYSCLKSOURCE_PLLCLK
board=custom

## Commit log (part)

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2026-05-31 Rename project from AERIS to T.H.E D.I.S.T.R.A.C.T.I.O.N
2026-06-23 Change project name to NOT-618
    Updated project title and description in README.
